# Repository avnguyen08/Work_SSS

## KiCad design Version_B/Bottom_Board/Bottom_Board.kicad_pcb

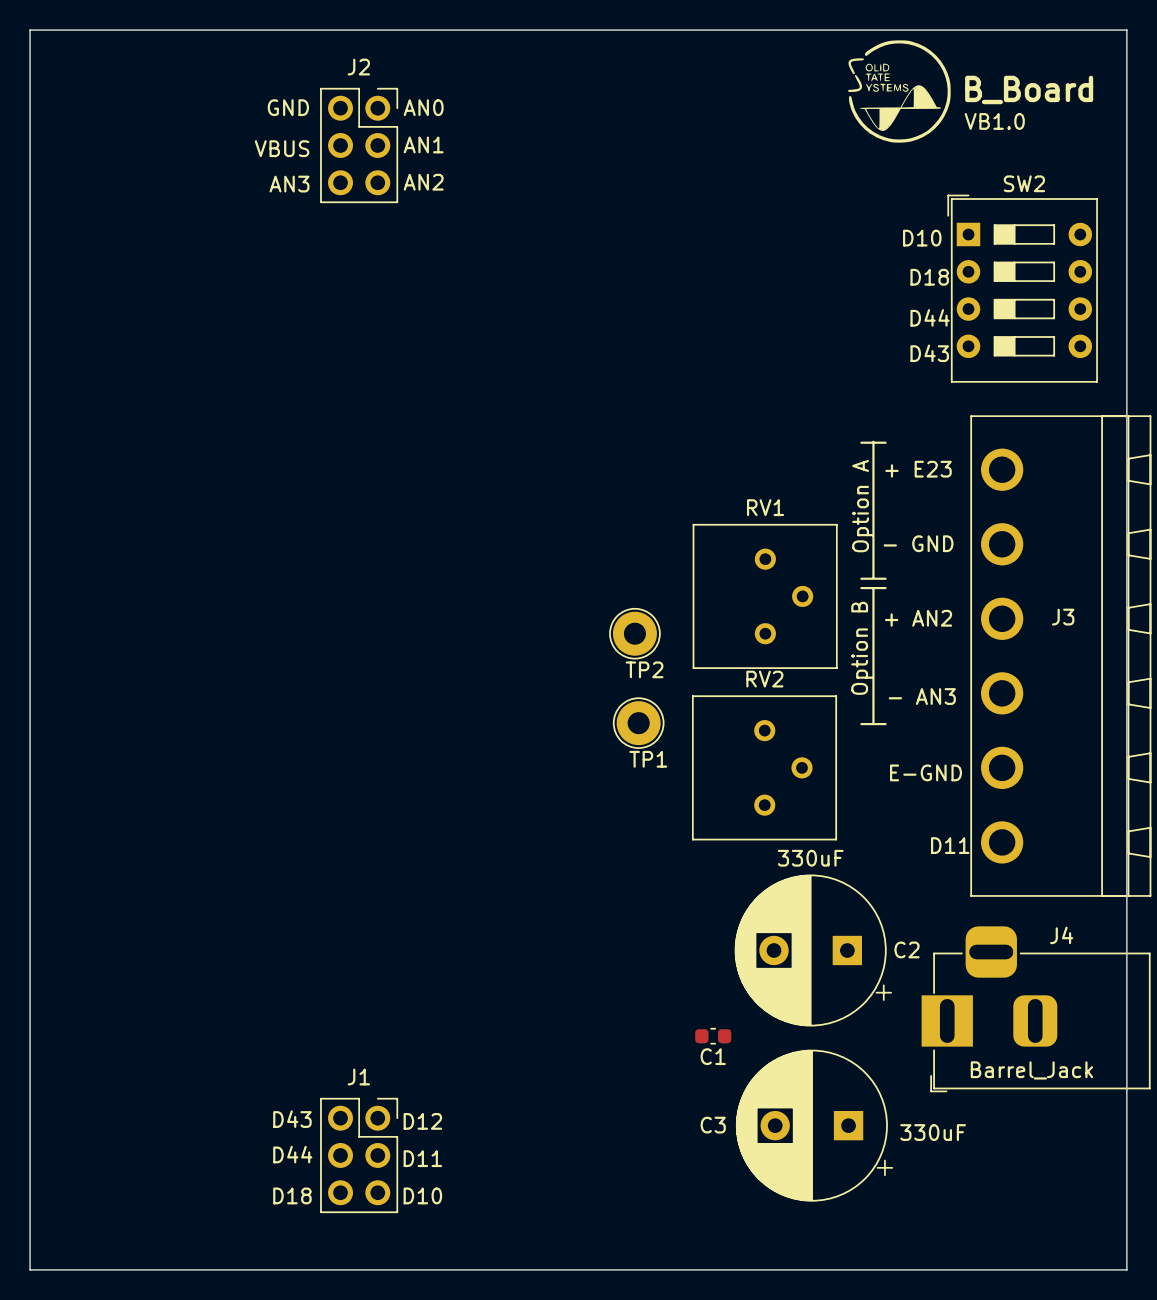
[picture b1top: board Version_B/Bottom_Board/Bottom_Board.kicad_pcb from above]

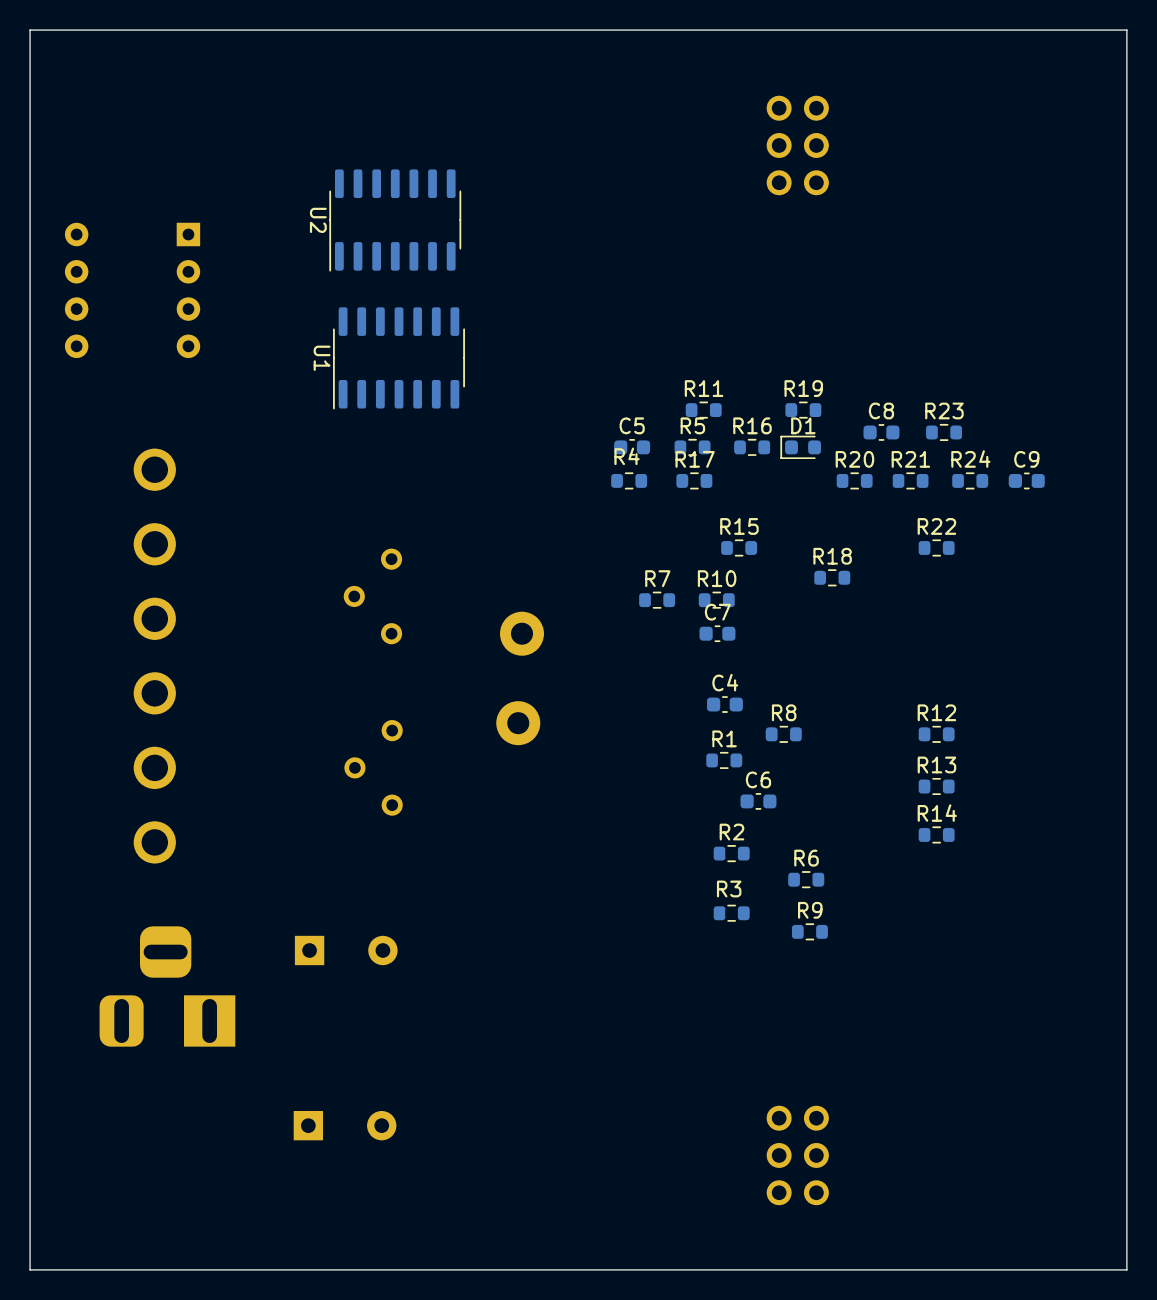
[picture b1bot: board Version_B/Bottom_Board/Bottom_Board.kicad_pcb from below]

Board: 2 copper layers, 74.8 x 84.5 mm, 45 parts (33 on the bottom side), 38 nets, no tracks yet.

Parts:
C1, C8, C9: .1uF; C_0603_1608Metric
C2, C3: 330uF; CP_Radial_D10.0mm_P5.00mm
C4, C6: 0.1uF; C_0603_1608Metric
C5: .002uF; C_0603_1608Metric
C7: 0.1 uF; C_0603_1608Metric
D1: 1N914; D_0603_1608Metric
J1, J2: Conn_02x03_Top_Bottom; PinSocket_2x03_P2.54mm_Vertical
J3: Screw_Terminal_01x06; PhoenixContact_MSTBA_2,5_6-G-5,08_1x06_P5.08mm_Horizontal
J4: Barrel_Jack; BarrelJack_Horizontal
R1, R20, R21, R22: 80.6K; R_0603_1608Metric
R2, R17: 4.7K; R_0603_1608Metric
R3, R9, R13, R14, R16, R19, R24: 10K; R_0603_1608Metric
R4: 30.1K; R_0603_1608Metric
R5: 20K; R_0603_1608Metric
R6: 1M; R_0603_1608Metric
R7: 25.5K; R_0603_1608Metric
R8: 3.65K; R_0603_1608Metric
R10: 187K; R_0603_1608Metric
R11: 110K; R_0603_1608Metric
R12: 16.2K; R_0603_1608Metric
R15, R18: 22K; R_0603_1608Metric
R23: 1.82K; R_0603_1608Metric
RV1, RV2: 20K; Potentiometer_Bourns_3386P_Vertical
SW2: SW_DIP_x04; SW_DIP_SPSTx04_Slide_9.78x12.34mm_W7.62mm_P2.54mm
TP1: .75 Vdc; TestPoint_Loop_D2.54mm_Drill1.5mm_Beaded
TP2: .55 Vdc; TestPoint_Loop_D2.54mm_Drill1.5mm_Beaded
U1, U2: LM324; SOIC-14_3.9x8.7mm_P1.27mm

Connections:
2x_OUTPUT: J2.1, R12.1, R13.2
4x_OUTPUT: R13.1, R14.2
+5V: R2.2, R15.1, U1.4 (V+), U2.4 (V+)
-5V: R3.1, R18.2, U1.11 (V-), U2.11 (V-)
AN1: C1.2, C2.2, C3.2, J2.2, J2.3, J3.2, J3.5, J4.2, J4.3, SW2.5, SW2.6, SW2.7, SW2.8
AN2: J2.5, J3.4
AN3: J2.6, J3.3
D10: J1.5, SW2.1
D11: J1.3, J3.1
D18: J1.6, SW2.2
D43: J1.2, SW2.4
D44: J1.4, SW2.3
E23_INPUT: J3.6, R4.1, R5.1
E60: C6.1, C7.2, C9.2, R4.2, R7.2, R9.1, R14.1, R17.2, R24.2
unnamed: C4.1, R8.2, R12.2, TP1.1, U2.7
unnamed: C4.2, R1.1, R22.1
unnamed: C7.1, R10.2
unnamed: C8.1, R23.2, U1.1
unnamed: C8.2, R20.2, R21.1
unnamed: D1.2 (A), U1.7
unnamed: D1.1 (K), R19.2, U1.12 (+)
unnamed: R2.1, RV1.1
unnamed: R3.2, RV1.3
unnamed: R6.2, RV1.2
unnamed: R7.1, R10.1
unnamed: R11.2, R16.1, U1.8
unnamed: R15.2, RV2.1
unnamed: R18.1, RV2.3
unnamed: C9.1, R21.2, U1.3 (+)
unnamed: R22.2, R23.1, R24.1, U1.2 (-)
unnamed: R17.1, U1.5 (+)
unnamed: R16.2, R19.1, RV2.2, U1.6 (-)
unnamed: C5.2, R5.2, U1.10 (+)
unnamed: C5.1, R11.1, U1.9 (-)
unnamed: R20.1, TP2.1, U1.13 (-), U1.14
unnamed: C6.2, R1.2, U2.5 (+)
unnamed: R6.1, R8.1, R9.2, U2.6 (-)
VBUS: C1.1, C2.1, C3.1, J2.4, J4.1

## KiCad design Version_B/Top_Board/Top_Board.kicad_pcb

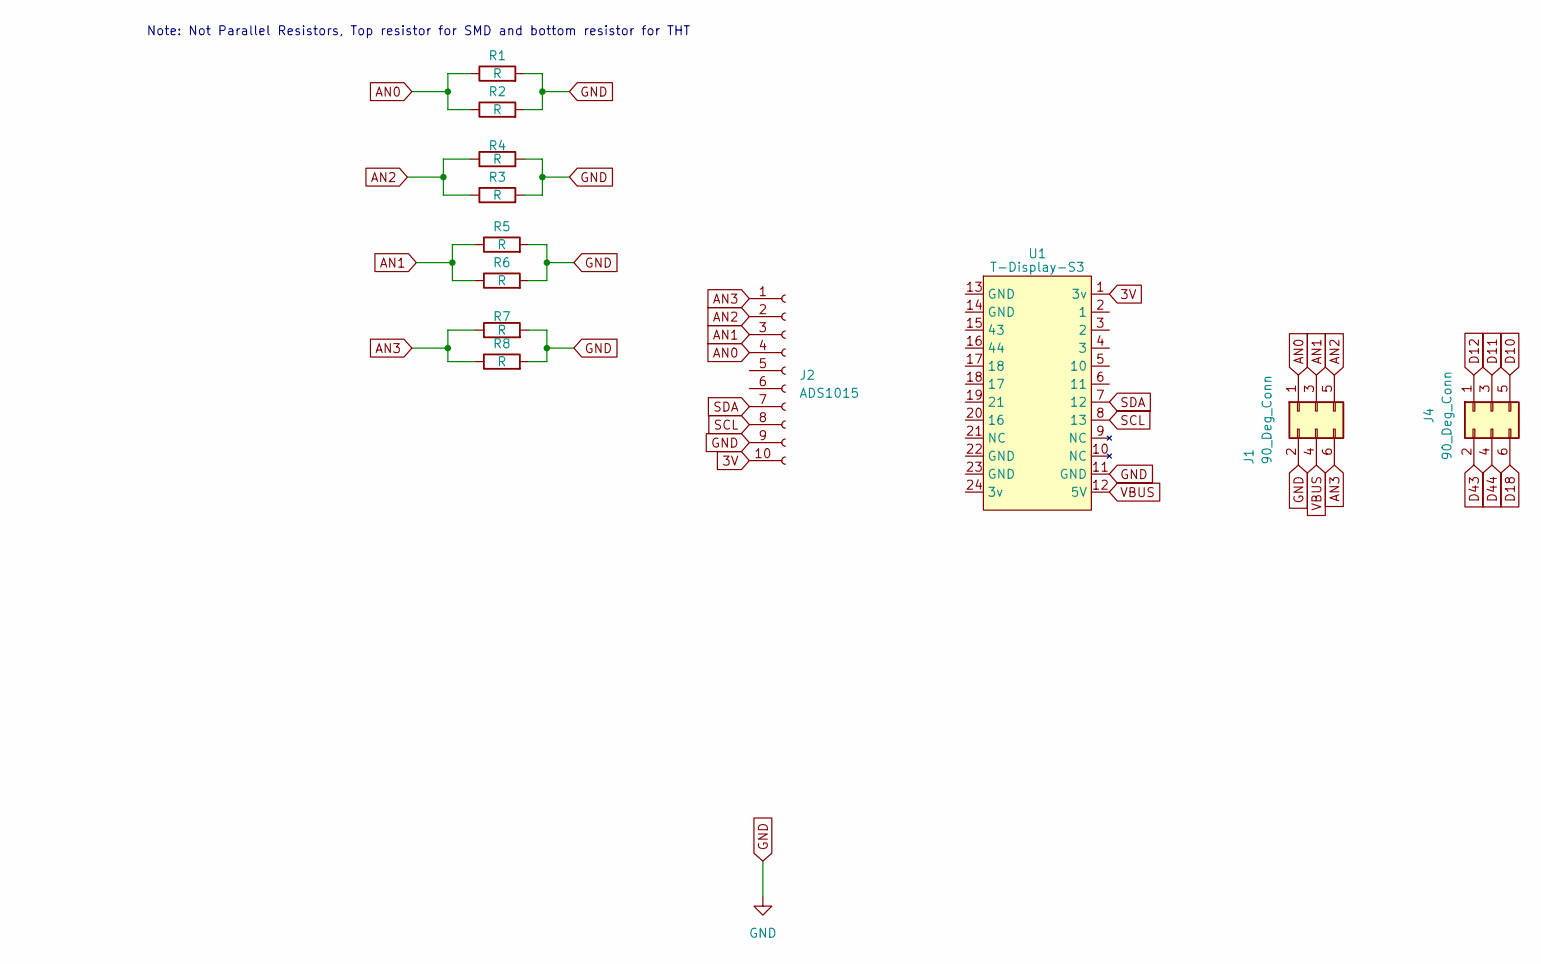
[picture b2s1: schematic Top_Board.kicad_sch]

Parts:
J1, J4: 90_Deg_Conn; PinHeader_2x03_P2.54mm_Horizontal
J2: ADS1015; PinSocket_1x10_P2.54mm_Vertical_1
R1, R4, R5, R7: R; R_0805_2012Metric
R2, R3, R6, R8: R; R_Axial_DIN0411_L9.9mm_D3.6mm_P12.70mm_Horizontal
U1: T-Display-S3

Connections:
3V: J2.10, U1.1 (3v)
AN0: J1.1, J2.4, R1.1, R2.1
AN1: J1.3, J2.3, R5.1, R6.1
AN2: J1.5, J2.2, R3.1, R4.1
AN3: J1.6, J2.1, R7.1, R8.1
D10: J4.1
D11: J4.3
D12: J4.5
D18: J4.6
D43: J4.2
D44: J4.4
GND: J1.2, J2.9, R1.2, R2.2, R3.2, R4.2, R5.2, R6.2, R7.2, R8.2, U1.11 (GND)
SCL: J2.8, U1.8 (13)
SDA: J2.7, U1.7 (12)
VBUS: J1.4, U1.12 (5V)

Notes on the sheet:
Note: Not Parallel Resistors, Top resistor for SMD and bottom resistor for THT

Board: 2 copper layers, 12 parts (11 on the bottom side), 9 nets, no tracks yet.

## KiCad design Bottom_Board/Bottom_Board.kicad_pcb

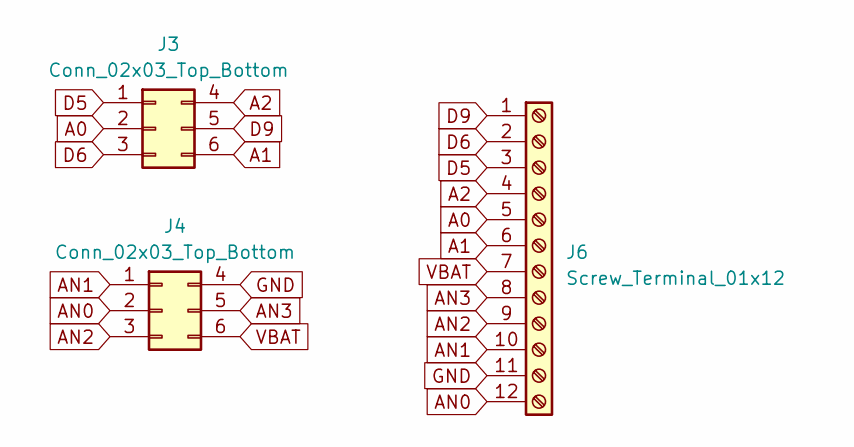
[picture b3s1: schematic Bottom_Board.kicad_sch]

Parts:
J3, J4: Conn_02x03_Top_Bottom; PinSocket_2x03_P2.54mm_Vertical
J6: Screw_Terminal_01x12; PhoenixContact_MSTBA_2,5_12-G-5,08_1x12_P5.08mm_Horizontal

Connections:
A0: J3.2, J6.5
A1: J3.6, J6.6
A2: J3.4, J6.4
AN0: J4.2, J6.12
AN1: J4.1, J6.10
AN2: J4.3, J6.9
AN3: J4.5, J6.8
D5: J3.1, J6.3
D6: J3.3, J6.2
D9: J3.5, J6.1
GND: J4.4, J6.11
VBAT: J4.6, J6.7

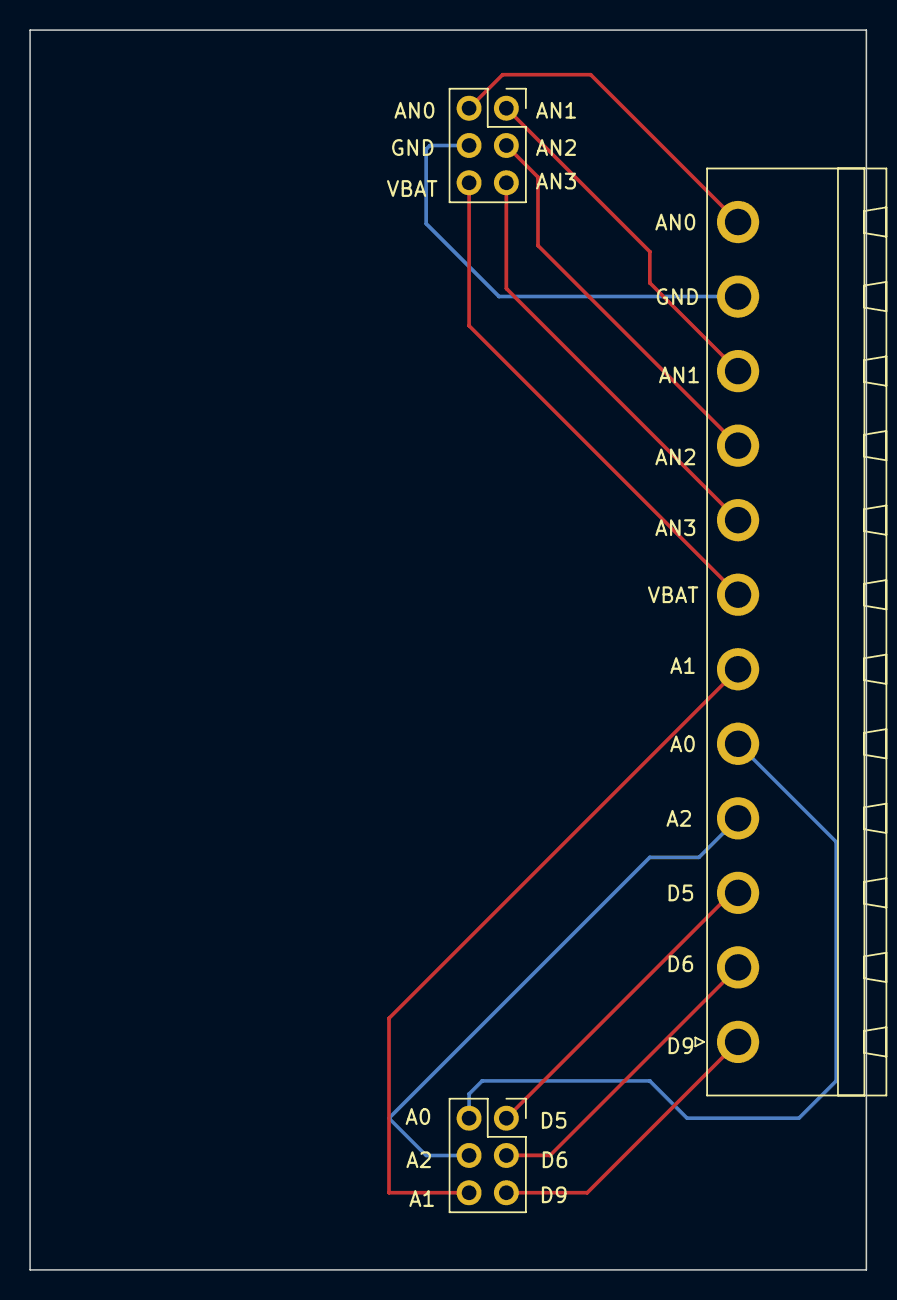
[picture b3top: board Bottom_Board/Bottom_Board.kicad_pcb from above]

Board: 2 copper layers, 57.0 x 84.5 mm, 3 parts (0 on the bottom side), 12 nets.

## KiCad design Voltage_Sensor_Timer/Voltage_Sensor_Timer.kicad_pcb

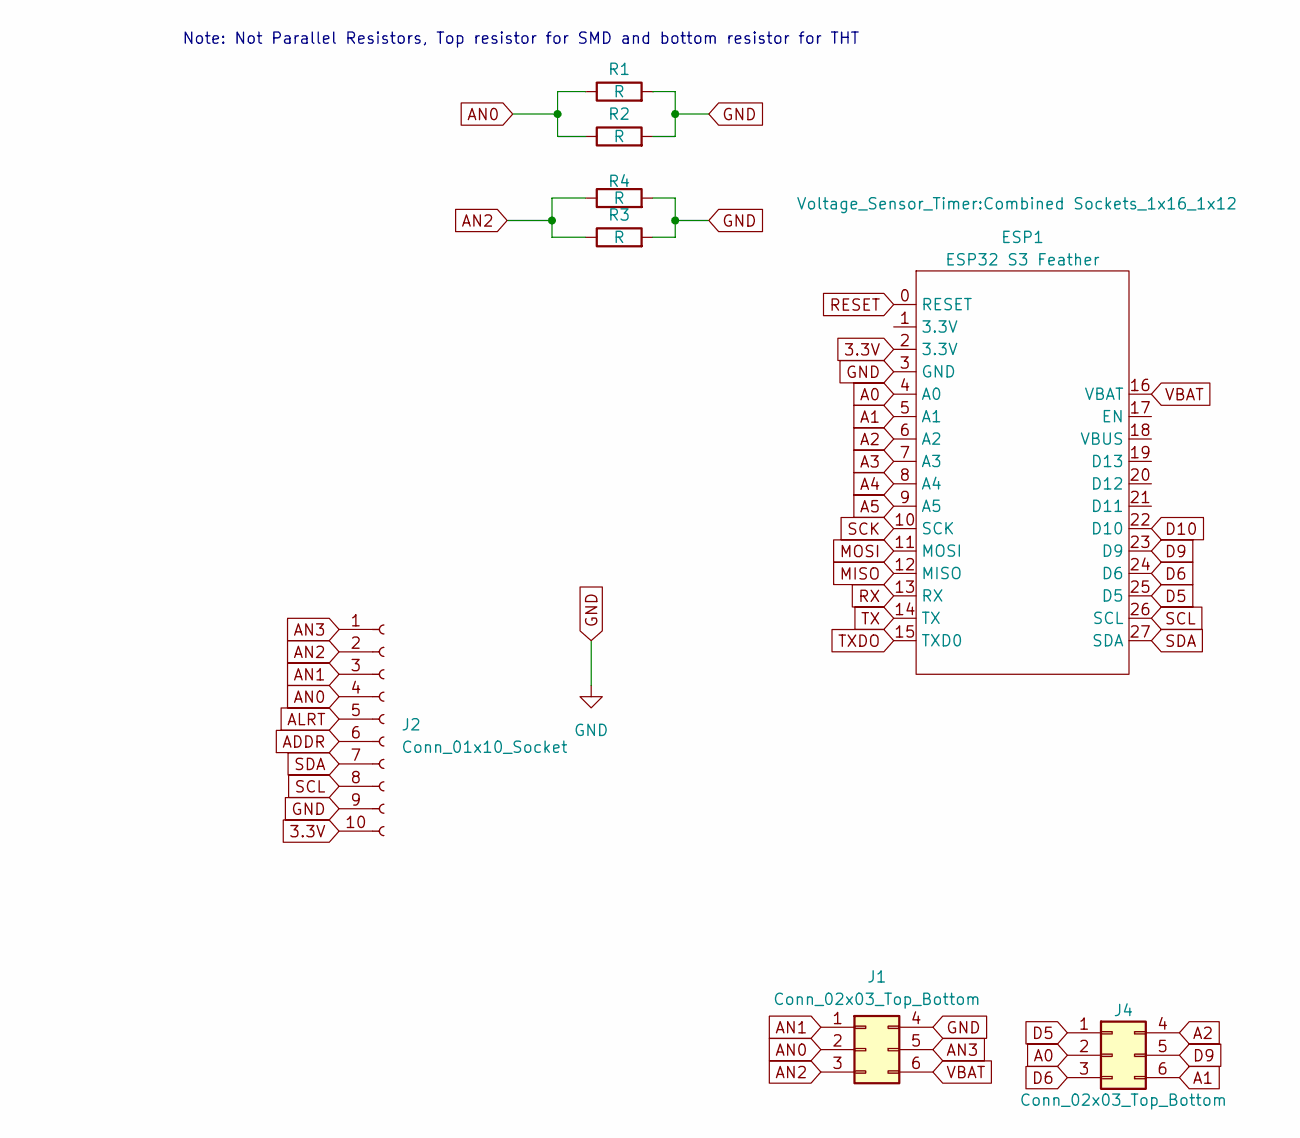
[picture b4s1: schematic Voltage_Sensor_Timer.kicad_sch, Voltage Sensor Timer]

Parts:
ESP1: ESP32 S3 Feather; Combined Sockets_1x16_1x12
J1, J4: Conn_02x03_Top_Bottom; PinHeader_2x03_P2.54mm_Horizontal
J2: Conn_01x10_Socket; PinSocket_1x10_P2.54mm_Vertical_1
R1, R4: R; R_0805_2012Metric
R2, R3: R; R_Axial_DIN0411_L9.9mm_D3.6mm_P12.70mm_Horizontal

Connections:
3.3V: ESP1.2 (3.3V), J2.10
A0: ESP1.4 (A0), J4.2
A1: ESP1.5 (A1), J4.6
A2: ESP1.6 (A2), J4.4
A3: ESP1.7 (A3)
A4: ESP1.8 (A4)
A5: ESP1.9 (A5)
ADDR: J2.6
ALRT: J2.5
AN0: J1.2, J2.4, R1.1, R2.1
AN1: J1.1, J2.3
AN2: J1.3, J2.2, R3.1, R4.1
AN3: J1.5, J2.1
D5: ESP1.25 (D5), J4.1
D6: ESP1.24 (D6), J4.3
D9: ESP1.23 (D9), J4.5
D10: ESP1.22 (D10)
GND: ESP1.3 (GND), J1.4, J2.9, R1.2, R2.2, R3.2, R4.2
MISO: ESP1.12 (MISO)
MOSI: ESP1.11 (MOSI)
RESET: ESP1.0 (RESET)
RX: ESP1.13 (RX)
SCK: ESP1.10 (SCK)
SCL: ESP1.26 (SCL), J2.8
SDA: ESP1.27 (SDA), J2.7
TX: ESP1.14 (TX)
TXDO: ESP1.15 (TXD0)
VBAT: ESP1.16 (VBAT), J1.6

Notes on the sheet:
Note: Not Parallel Resistors, Top resistor for SMD and bottom resistor for THT

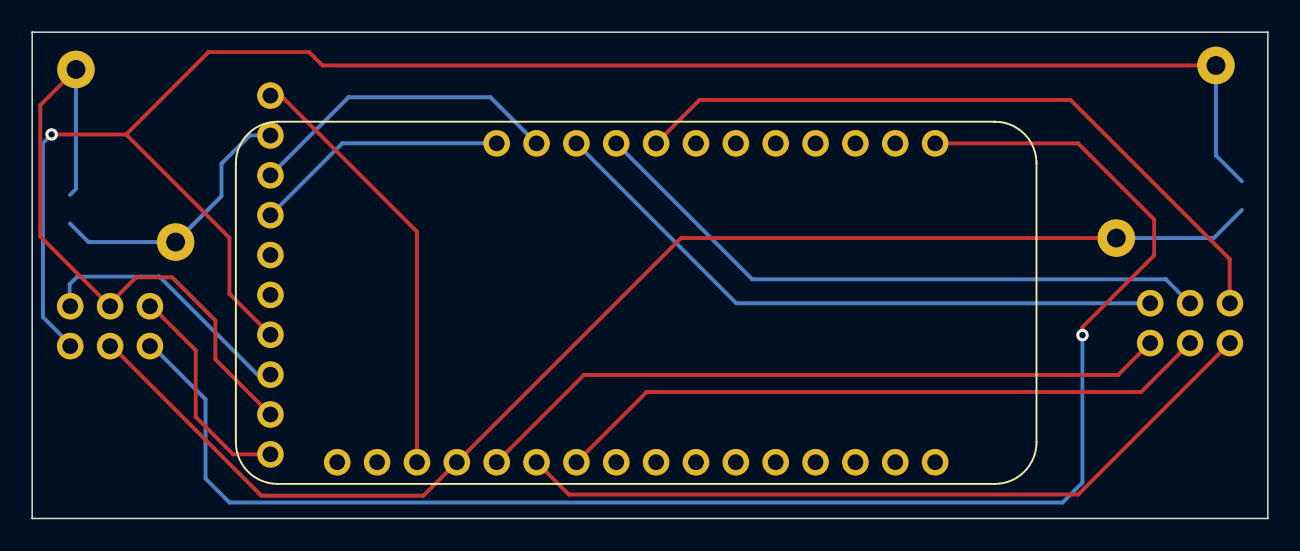
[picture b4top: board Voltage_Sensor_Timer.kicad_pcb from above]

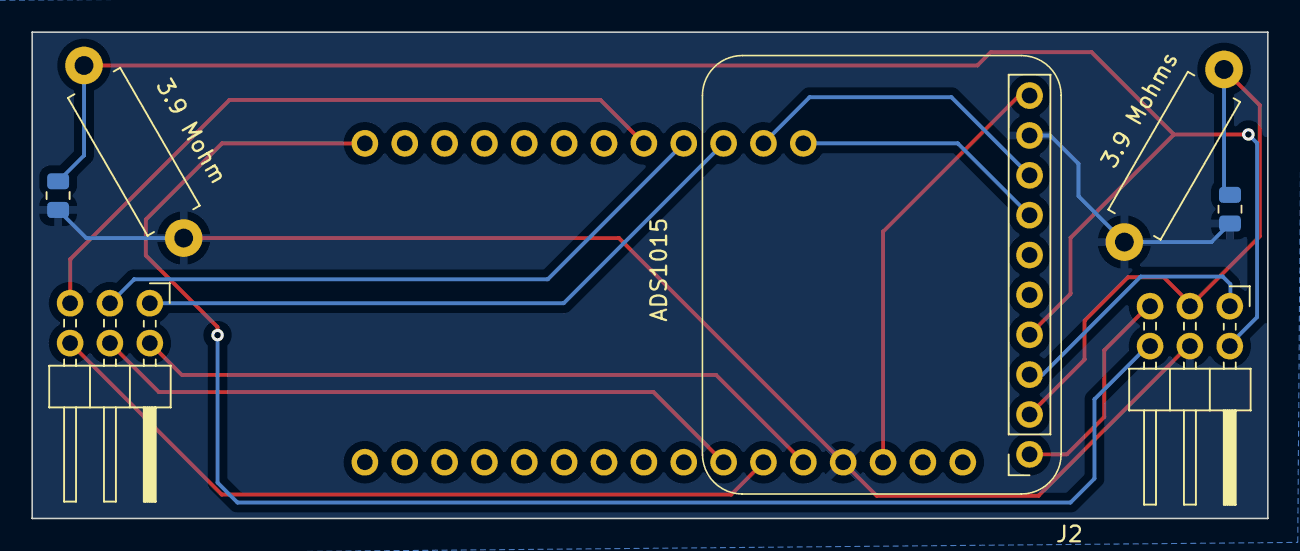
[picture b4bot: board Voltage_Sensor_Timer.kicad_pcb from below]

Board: 2 copper layers, 78.7 x 31.0 mm, 8 parts (7 on the bottom side), 15 nets.

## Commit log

2023-11-08 start
2023-11-27 Clean directory
2023-11-29 updated hardware, cleaned up
2023-12-18 Reworked library into Ver 0,A,B,C
